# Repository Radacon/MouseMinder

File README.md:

# MouseMinder

MouseMinder is a small ATtiny10-based hardware project with a matching programming and test fixture. This repository combines the PCB design, fixture firmware, operator GUI, mechanical CAD exports, and simulation or validation data used to build and test the device.

## Repository Layout

- `codebase/`
  - Arduino Uno fixture firmware in `ardu_tiny_toaster.ino`
  - Base TPI programmer implementation in `tiny10_base_code.ino`
  - Operator desktop GUI in `gui.py`
  - Early or alternate device firmware work under `AtmelStudio/`
- `pcb_design/`
  - Main MouseMinder KiCad project files:
    - `MouseMinder.kicad_sch`
    - `MouseMinder.kicad_pcb`
    - `MouseMinder.kicad_pro`
  - Fixture or shield PCB design under `MouseMinder_Programmer_Shield/`
  - Archived KiCad backups under `MouseMinder-backups/`
  - Older release archives under `mouseminder_prev_versions/`
- `mechanical_design/`
  - Enclosure and trap body STEP exports under `trap_body/`
  - Accessory parts such as the battery isolator under `accessories/`
- `sim_and_test/`
  - Power profiling captures under `PowerProfilerData/`
  - Simulation exports under `Simulation/`

## Hardware Overview

The main board centers on an `ATtiny10-TS` and includes:

- A coin-cell battery holder
- A buzzer
- An LED indicator
- Two pushbuttons
- A discrete power or latching section around `Q1`

The repository also includes a separate programmer shield design and a fixture workflow for flashing and validating boards during bring-up or production.

## PCB Design Files

Primary electrical design assets live in `pcb_design/`:

- `MouseMinder.kicad_sch`
- `MouseMinder.kicad_pcb`
- `MouseMinder.kicad_pro`

Related hardware history is split out into:

- `pcb_design/MouseMinder_Programmer_Shield/` for the programming fixture PCB
- `pcb_design/MouseMinder-backups/` for KiCad backup archives
- `pcb_design/mouseminder_prev_versions/` for older packaged revisions

## Firmware And GUI

The programming and test fixture is built around an Arduino Uno and a Python desktop GUI.

Arduino-side files in `codebase/`:

- `ardu_tiny_toaster.ino`: fixture control firmware
- `tiny10_base_code.ino`: base TPI programming support for ATtiny4/5/9/10/20/40 devices

Desktop-side files in `codebase/`:

- `gui.py`: operator GUI for selecting firmware, discovering the fixture over serial, and running the programming loop
- `requirements.txt`: original behavior notes for the GUI and fixture

There is also an Atmel Studio project under `codebase/AtmelStudio/MouseMinder/` with a `main.c` firmware entry point and generated debug outputs.

## Fixture I/O Mapping

The current fixture firmware uses:

- `D10` -> `!RST`
- `D11/D12` -> `TPIDATA`
- `D13` -> `TPICLK`
- `A0` -> `BATT`
- `A1` -> `LATCHED`

The operator GUI is intended to:

- Auto-discover the Arduino fixture over available COM ports
- Show connection and pin-state information
- Let the operator select a `.hex` file
- Run the detect, program, verify, and test loop

## Mechanical Assets

Mechanical CAD exports are grouped under `mechanical_design/`:

- `trap_body/` contains enclosure and body STEP files, including lid and clip geometry
- `accessories/` contains supporting parts such as `Battery_Isolator_debossed.STEP`

## Simulation And Validation Data

Supporting measurement and simulation files live in `sim_and_test/`:

- `PowerProfilerData/` contains sleep-current or power measurement CSV files
- `Simulation/` contains scope and waveform export data from circuit simulation work

## Typical Workflow

1. Open the main hardware in `pcb_design/MouseMinder.kicad_sch` and `pcb_design/MouseMinder.kicad_pcb`.
2. Load the Arduino fixture firmware from `codebase/ardu_tiny_toaster.ino`.
3. Launch the operator GUI from `codebase/gui.py`.
4. Connect the programming fixture and target board.
5. Select a target `.hex` file and run the programming and test cycle.

## Running The GUI

Install the required Python package, then launch the GUI:

```powershell
pip install pyserial
python codebase\gui.py
```

The GUI depends on:

- `pyserial`
- Python standard library `tkinter`

## Fastest Entry Points

If you are picking up the project fresh, start with:

- `pcb_design/MouseMinder.kicad_sch`
- `pcb_design/MouseMinder.kicad_pcb`
- `codebase/ardu_tiny_toaster.ino`
- `codebase/gui.py`

## PMS150C Firmware Releases

Production PMS150C firmware is published only from tags named `firmware-vMAJOR.MINOR.PATCH` that point to a commit already on `main`. The tag-only GitHub Actions workflow builds `codebase/VSCODE_FreePDK` and publishes three immutable release assets:

- `slowclocksleep_PMS150C.bin`
- `slowclocksleep_PMS150C.bin.sha256`
- `mouseminder-firmware.json`

The manifest records the full commit, build toolchain, PMS150C memory contract, calibration target, asset size, and SHA-256. The production programmer must still require explicit WordPress administrator approval and verify the downloaded binary against the approved manifest before programming.

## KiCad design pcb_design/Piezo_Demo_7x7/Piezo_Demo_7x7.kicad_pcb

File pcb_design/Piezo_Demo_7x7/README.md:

# Piezo Demo 7x7

- KiCad 9 schematic and fully routed two-layer PCB.
- 224 mm x 224 mm board with a 7 x 7 grid of 32 mm cells.
- 43 buzzer footprints, two rows of seven MouseMinder SMD selector buttons, a vertical BNC input, and a reserved switching/MCU cell.
- Available EasyEDA 3D bodies are included and linked project-relatively.
- The BNC includes a simplified project-local preview body based on the TE product envelope.
- Front silkscreen: cell and MPN.
- Back silkscreen: MPN, LCSC number, live LCSC 1-piece/500-piece unit pricing, voltage, current, SPL, driver type, mount, and body size.

Five unavailable EasyEDA records use same-family fallback geometry. Verify every footprint against the purchased part's current datasheet before fabrication.

The schematic directly connects the BNC through one selected row switch and one selected column switch. Press one button from each bank to connect the corresponding buzzer. G2-G7 are unused.

ERC and PCB DRC both pass with zero violations and zero unconnected pads. JLCPCB-ready Gerbers are in `fabrication/Piezo_Demo_7x7_JLCPCB_Gerbers.zip`.

Regenerate with KiCad's bundled Python:

```powershell
python .\generate_bnc_model.py
& 'C:\Program Files\KiCad\9.0\bin\python.exe' .\generate_piezo_demo_board.py
python .\generate_piezo_demo_schematic.py
```

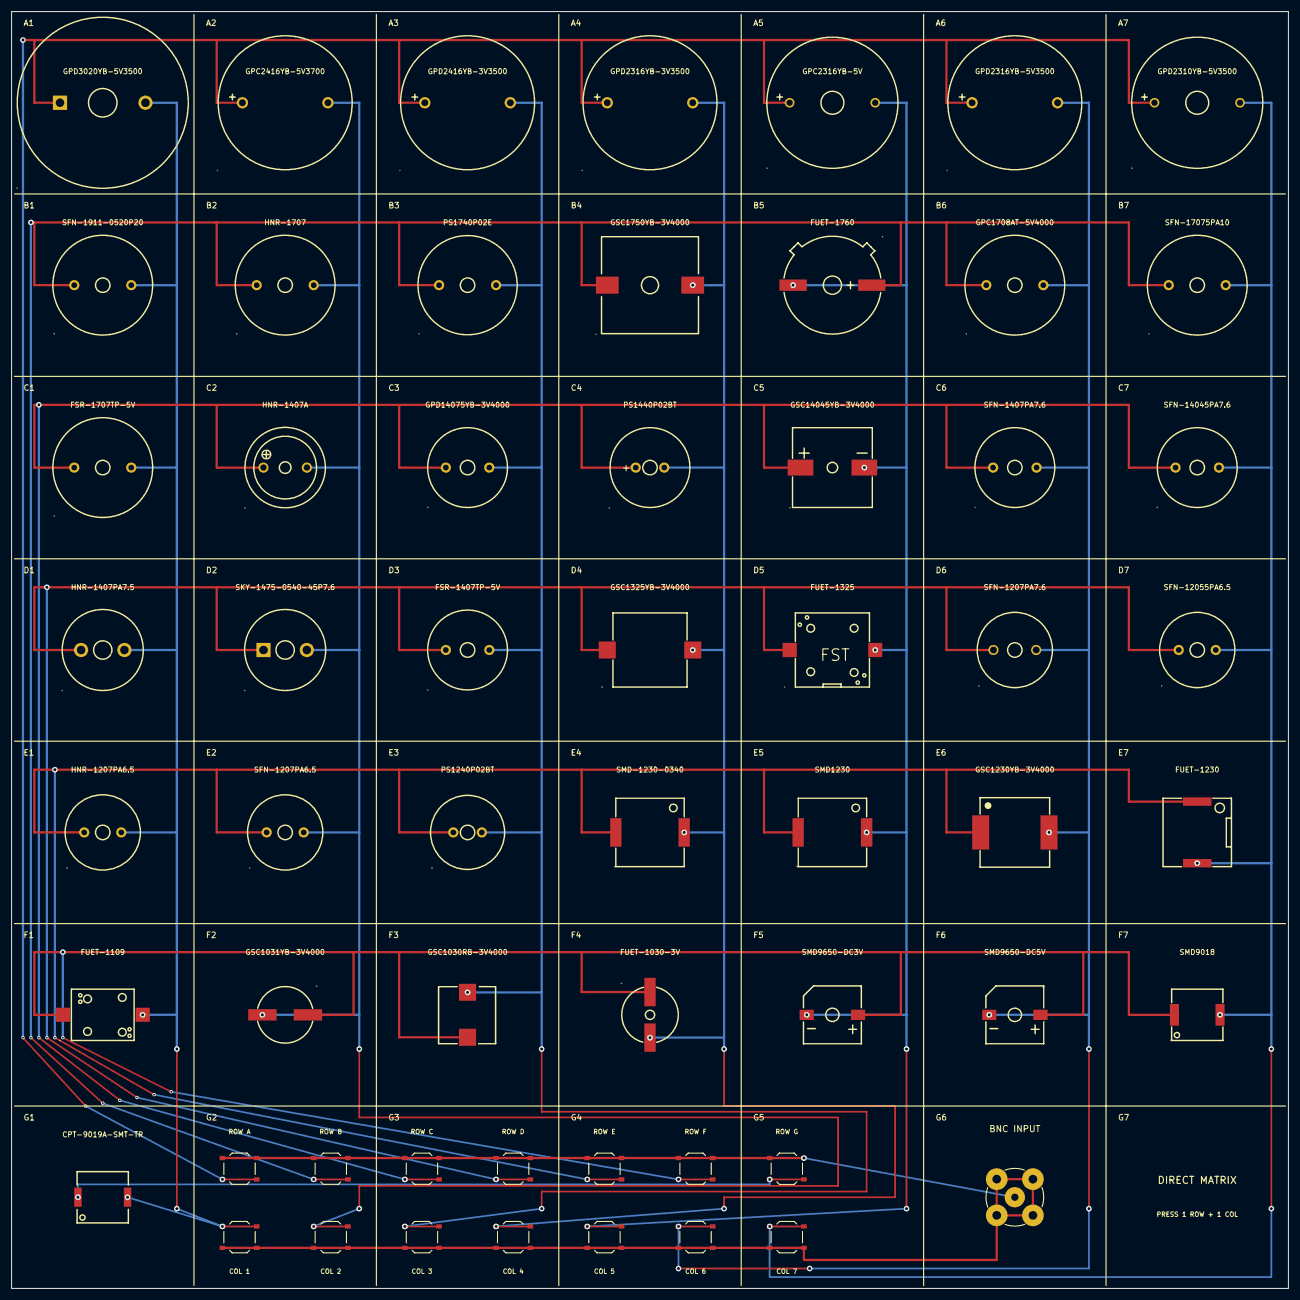
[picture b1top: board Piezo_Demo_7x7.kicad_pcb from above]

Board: 2 copper layers, 224.0 x 224.0 mm, 58 parts (0 on the bottom side), 16 nets.

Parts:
BZ1: GPD3020YB-5V3500; BUZ-TH_BD30.0-P15.00-D0.8
BZ2: GPC2416YB-5V3700; BUZ-TH_BD23.5-P15.00-D0.8-FD
BZ3: GPD2416YB-3V3500; BUZ-TH_BD23.5-P15.00-D0.8-FD
BZ4: GPD2316YB-3V3500; BUZ-TH_BD23.5-P15.00-D0.8-FD
BZ5: GPC2316YB-5V; BUZ-TH_BD23.0-P15.00-D0.8-FD
BZ6: GPD2316YB-5V3500; BUZ-TH_BD23.5-P15.00-D0.8-FD
BZ7: GPD2310YB-5V3500; BUZ-TH_BD23.0-P15.00-D0.8-FD
BZ8: SFN-1911-0520P20; BUZ-TH_BD17.0-P10.00-D0.9
BZ9: HNR-1707; BUZ-TH_BD17.0-P10.00-D0.9
BZ10: PS1740P02E; BUZ-TH_BD17.0-P10.00-D0.8
BZ11: GSC1750YB-3V4000; BUZ-SMD_L17.0-W17.0
BZ12: FUET-1760; BUZZ-SMD_FUET-1760
BZ13: GPC1708AT-5V4000; BUZ-TH_BD17.0-P10.00-D0.9
BZ14: SFN-17075PA10; BUZ-TH_BD17.0-P10.00-D0.9
BZ15: FSR-1707TP-5V; BUZ-TH_BD17.0-P10.00-D0.9
BZ16: HNR-1407A; BUZ-TH_BD14.1-P7.62-D1.0-FD
BZ17: GPD14075YB-3V4000; BUZ-TH_BD14.0-P7.60-D0.7-FD
BZ18: PS1440P02BT; BUZ-TH_BD14.0-P5.00-D0.7-FD
BZ19: GSC14045YB-3V4000; BUZ-SMD_L14.1-W14.1-LS14.9
BZ20: SFN-1407PA7.6; BUZ-TH_BD14.0-P7.60-D0.7
BZ21: SFN-14045PA7.6; BUZ-TH_BD14.0-P7.60-D0.7
BZ22: HNR-1407PA7.5; BUZ-TH_BD14.0-P7.60-D0.8-L
BZ23: SKY-1475-0540-45P7.6; BUZ-TH_BD14.0-P7.60-D1.0-L
BZ24: FSR-1407TP-5V; BUZ-TH_BD14.0-P7.60-D0.7
BZ25: GSC1325YB-3V4000; BUZ-SMD_L13.0-W13.0
BZ26: FUET-1325; BUZ-SMD_FST-1325
BZ27: SFN-1207PA7.6; BUZ-TH_BD12.6-P7.50-D0.9
BZ28: SFN-12055PA6.5; BUZ-TH_BD12.5-P6.50-D0.9
BZ29: HNR-1207PA6.5; BUZ-TH_BD12.5-P6.50-D0.9
BZ30: SFN-1207PA6.5; BUZ-TH_BD12.5-P6.50-D0.9
BZ31: PS1240P02BT; BUZ-TH_BD12.5-P5.00-D0.9
BZ32: SMD-1230-0340; BUZ-SMD_L12.0-W12.0
BZ33: SMD1230; BUZ-SMD_L12.0-W12.0
BZ34: GSC1230YB-3V4000; BUZ-SMD_L12.0-W12.0_CPT-12123-81-SMT-TR
BZ35: FUET-1230; BUZ-SMD_L12.0-W12.0_FUET-1230
BZ36: FUET-1109; BUZ-SMD_FST-1109
BZ37: GSC1031YB-3V4000; BUZ-SMD_BD10.0-P8.00-LS11.0
BZ38: GSC1030RB-3V4000; BUZ-SMD_L10.0-W10.0_GSC1030RB-3V4000
BZ39: FUET-1030-3V; BUZ-SMD_FUET-1030-XXV
BZ40: SMD9650-DC3V; BUZ-SMD_L9.6-W9.6-LS10.0-R
BZ41: SMD9650-DC5V; BUZ-SMD_L9.6-W9.6-LS10.0-R
BZ42: SMD9018; BUZ-SMD_L9.0-W9.0-P8.00-LS9.3
BZ43: CPT-9019A-SMT-TR; BUZ-SMD_L9.0-W9.0_CPT-9019A-SMT-TR
J1: 1-1478204-0; BNC_TEConnectivity_1478204_Vertical
SW1, SW2, SW3, SW4, SW5, SW6, SW7, SW8, SW9, SW10, SW11, SW12, SW13, SW14: LCK-TA022H18-2WL; SW_Push_1P1T_XKB_TS-1187A

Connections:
BNC_RETURN: J1.2, SW8.2, SW9.2, SW10.2, SW11.2, SW12.2, SW13.2, SW14.2
BNC_SIGNAL: J1.1, SW1.1, SW2.1, SW3.1, SW4.1, SW5.1, SW6.1, SW7.1
COL_1: BZ1.2, BZ8.2, BZ15.2, BZ22.2, BZ29.2, BZ36.2, BZ43.2, SW8.1
COL_2: BZ2.2, BZ9.2, BZ16.2, BZ23.2, BZ30.2, BZ37.2, SW9.1
COL_3: BZ3.2, BZ10.2, BZ17.2, BZ24.2, BZ31.2, BZ38.2, SW10.1
COL_4: BZ4.2, BZ11.2, BZ18.2, BZ25.2, BZ32.2, BZ39.2, SW11.1
COL_5: BZ5.2, BZ12.2, BZ19.2, BZ26.2, BZ33.2, BZ40.2, SW12.1
COL_6: BZ6.2, BZ13.2, BZ20.2, BZ27.2, BZ34.2, BZ41.2, SW13.1
COL_7: BZ7.2, BZ14.2, BZ21.2, BZ28.2, BZ35.2, BZ42.2, SW14.1
ROW_A: BZ1.1, BZ2.1, BZ3.1, BZ4.1, BZ5.1, BZ6.1, BZ7.1, SW1.2
ROW_B: BZ8.1, BZ9.1, BZ10.1, BZ11.1, BZ12.1, BZ13.1, BZ14.1, SW2.2
ROW_C: BZ15.1, BZ16.1, BZ17.1, BZ18.1, BZ19.1, BZ20.1, BZ21.1, SW3.2
ROW_D: BZ22.1, BZ23.1, BZ24.1, BZ25.1, BZ26.1, BZ27.1, BZ28.1, SW4.2
ROW_E: BZ29.1, BZ30.1, BZ31.1, BZ32.1, BZ33.1, BZ34.1, BZ35.1, SW5.2
ROW_F: BZ36.1, BZ37.1, BZ38.1, BZ39.1, BZ40.1, BZ41.1, BZ42.1, SW6.2
ROW_G: BZ43.1, SW7.2

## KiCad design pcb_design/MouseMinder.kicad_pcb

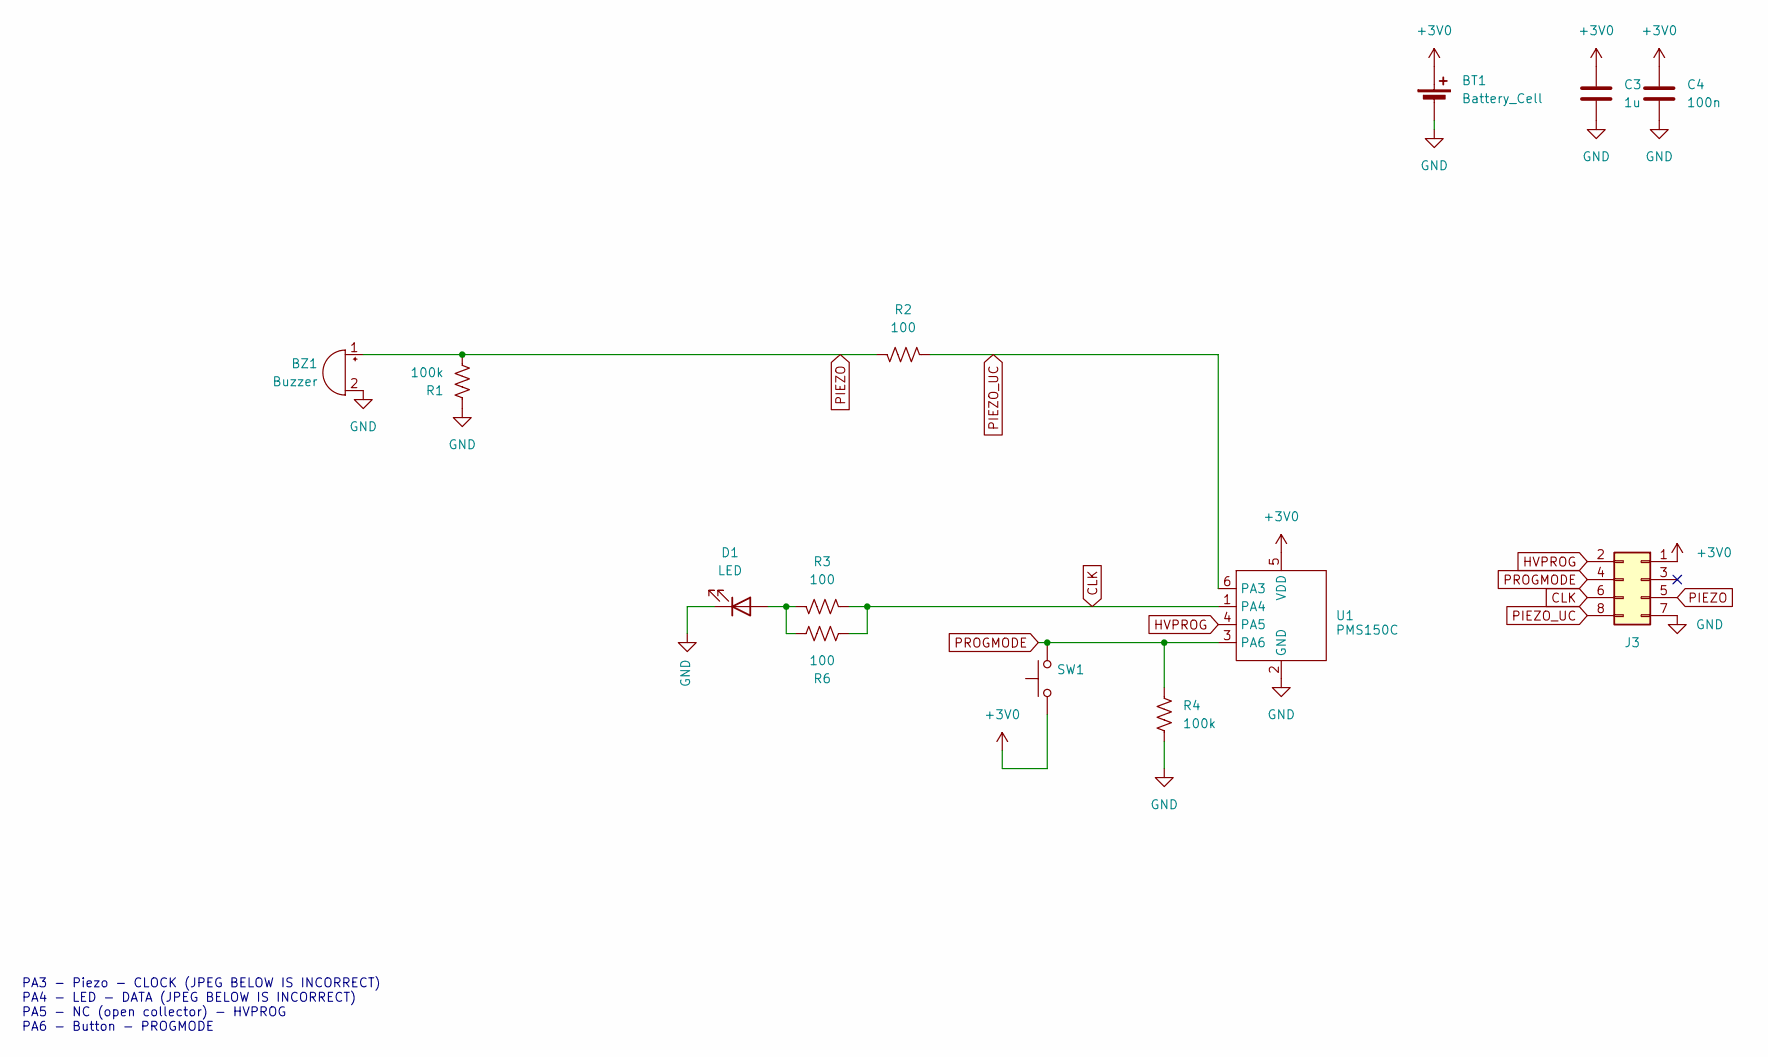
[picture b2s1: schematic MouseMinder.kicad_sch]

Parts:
BT1: Battery_Cell; MY-2032-08; MPN C964832; JLC_MPN C964832
BZ1: Buzzer; GSC1230YB-3V4000; MPN C255333; JLC_MPN C255333
C3: 1u; C_0603_1608Metric; MPN C1592; JLC_MPN C1592
C4: 100n; C_0603_1608Metric; MPN C2909627; JLC_MPN C2909627
D1: LED; XL-2810UYC; MPN C3646949; JLC_MPN C3646949
J3: Conn_02x04_Odd_Even; 2x8_POGO_CENTERING_HOLES
R1, R4: 100k; R_0603_1608Metric; MPN C25803; JLC_MPN C25803
R2, R3, R6: 100; R_0603_1608Metric; MPN C2785067; JLC_MPN C2785067
SW1: LCK-TA022H18-2WL; SW_Push_1P1T_XKB_TS-1187A; MPN C51978285; JLC_MPN C51978285
U1: PMS150C; SOT-23-6; MPN C168658; JLC_MPN C168658

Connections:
+3V0: BT1.1 (+), C3.1, C4.1, J3.1, SW1.1, U1.5 (VDD)
CLK: J3.6, R3.1, R6.1, U1.1 (PA4)
GND: BT1.2 (-), BZ1.2 (-), C3.2, C4.2, D1.1 (K), J3.7, R1.1, R4.2, U1.2 (GND)
HVPROG: J3.2, U1.4 (PA5)
unnamed: D1.2 (A), R3.2, R6.2
PIEZO: BZ1.1 (+), J3.5, R1.2, R2.2
PIEZO_UC: J3.8, R2.1, U1.6 (PA3)
PROGMODE: J3.4, R4.1, SW1.2, U1.3 (PA6)

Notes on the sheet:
PA3 - Piezo - CLOCK (JPEG BELOW IS INCORRECT) PA4 - LED - DATA (JPEG BELOW IS INCORRECT) PA5 - NC (open collector) - HVPROG PA6 - Button - PROGMODE

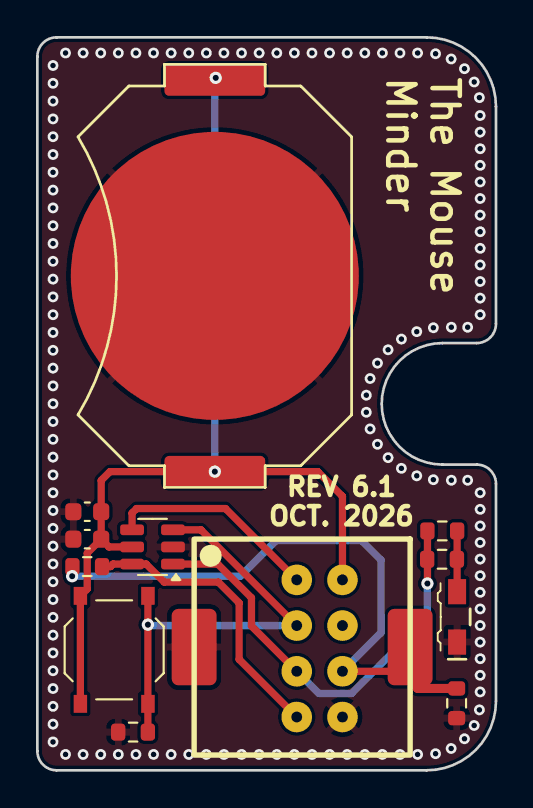
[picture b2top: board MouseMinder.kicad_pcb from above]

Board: 2 copper layers, 25.5 x 40.7 mm, 13 parts (1 on the bottom side), 8 nets.

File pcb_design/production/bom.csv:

Designator,Footprint,Quantity,Value,LCSC Part #
BT1,MY-2032-08,1,Battery_Cell,C964831 
BZ1,GSC1230YB-3V4000,1,Buzzer,C255333
C3,0603,1,1u,C1592
C4,0603,1,100n,C14663
D1,XL-2810UYC,1,LED,C3646949
"R1, R4",0603,2,100k,C25803
"R2, R3, R6",0603,3,100,C22775
SW1,SW_Push_1P1T_XKB_TS-1187A,1,LCK-TA022H18-2WL,C51978285
U1,SOT-23-6,1,PMS150C,C168658

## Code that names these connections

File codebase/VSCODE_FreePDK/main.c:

/*
  MouseMinder low-power alarm

  PMS150C-U06

  PA6: sleep/wake pushbutton, externally pulled low, switch to VDD
  PA4: LED, active high
  PA3: piezo input while quiet; Timer2 tone output while sounding
*/

#include <stdint.h>
#include "sdcc_intellisense.h"
#include <pdk/device.h>

#include "auto_sysclock.h"
#include "startup.h"
#include "delay.h"
#include "chirp_pattern.h"

#if CHIRP_MASTER_CLOCK_HZ != F_CPU
#error "chirp_pattern.h clock does not match the firmware F_CPU"
#endif

#if CHIRP_TIMER_DIVIDER != 1
#error "The firmware chirp player currently requires timer divider 1"
#endif

/*------------------------------------------------------------------
  User tuning
 ------------------------------------------------------------------*/

#define LED_PULSE_MS               10u
#define EVENT_SLEEP_MS           1000u
#define LED_FLASHES_PER_CHIRP       5u

/*------------------------------------------------------------------
  Pins
 ------------------------------------------------------------------*/

#define PIEZO_BIT                   3u
#define LED_BIT                     4u
#define BUTTON_BIT                  6u

#define PIEZO_MASK          (1u << PIEZO_BIT)
#define LED_MASK            (1u << LED_BIT)
#define BUTTON_MASK         (1u << BUTTON_BIT)

#define turnLedOn()         (PA |= LED_MASK)
#define turnLedOff()        (PA &= (uint8_t)~LED_MASK)
#define buttonIsPressed()   ((PA & BUTTON_MASK) != 0)

/*------------------------------------------------------------------
  Timer16 timed STOPEXE sleep
 ------------------------------------------------------------------*/

/*
 * Timer16 uses undivided ILRC and wakes on the rising edge of bit 15.
 * Each preload stays below 0x8000, making that rising edge the next bit-15
 * transition.  Longer delays are split into 500 ms sleeps below.
 */
#define TIMER16_SLEEP_CONFIG \
    (T16M_CLK_ILRC | T16M_CLK_DIV1 | T16M_INTSRC_15BIT)

#if (F_CPU % 1000u) != 0
#error "Timer16 millisecond sleeps require F_CPU divisible by 1000"
#endif

#define ILRC_TICKS_PER_MS (F_CPU / 1000u)

#if ILRC_TICKS_PER_MS != 52u
#error "Update millisecondsToTicks for the configured F_CPU"
#endif

static uint16_t timer16Load;

static void piezoInput(void)
{
    TM2C = TM2C_CLK_DISABLE;
    INTRQ &= (uint8_t)~INTRQ_TM2;
    PA &= (uint8_t)~PIEZO_MASK;
    PAC &= (uint8_t)~PIEZO_MASK;
}

static uint8_t activeLedPulseDelay(void)
{
    PADIER = BUTTON_MASK;

    /*
     * This helper is used only with compile-time constants.  Staying awake
     * here matches the ATtiny's _delay_ms() cadence and avoids PMS150C
     * STOPEXE wake-up latency on short delays.
     */
    _delay_ms(LED_PULSE_MS);

    return buttonIsPressed();
}

static uint8_t sleepTicks(uint16_t ticks, uint8_t piezoWake)
{
    uint8_t buttonPressed;

    T16M = (uint8_t)TIMER16_SLEEP_CONFIG;
    timer16Load = (uint16_t)(32768u - ticks);
    __asm
        stt16 _timer16Load
    __endasm;
    INTEGS &= (uint8_t)~INTEGS_T16_FALLING;
    INTRQ &= (uint8_t)~INTRQ_T16;

    /*
     * PA6 always wakes active waits.  PA3 also wakes quiet waits, but is
     * excluded while Timer2 is driving the tone.
     */
    PADIER = (uint8_t)(BUTTON_MASK |
                      (piezoWake ? PIEZO_MASK : (uint8_t)0u));

    __asm
        stopexe
    __endasm;

    /* Read PA6 before disabling its digital input buffer. */
    buttonPressed = buttonIsPressed();
    PADIER = 0;
    INTRQ &= (uint8_t)~INTRQ_T16;

    return buttonPressed;
}

static uint8_t sleepMilliseconds(uint16_t milliseconds, uint8_t piezoWake)
{
    uint16_t ticks;

    while (milliseconds > 500u)
    {
        if (sleepTicks((uint16_t)(F_CPU / 2u), piezoWake))
            return 1;

        milliseconds -= 500u;
    }

    if (!milliseconds)
        return 0;

    /* 52 ticks/ms = 32 + 16 + 4; avoid SDCC's multiply helper. */
    ticks = (uint16_t)((milliseconds << 5) +
                       (milliseconds << 4) +
                       (milliseconds << 2));

    return sleepTicks(ticks, piezoWake);
}

/*------------------------------------------------------------------
  Piezo tone
 ------------------------------------------------------------------*/

static void startTone(uint8_t timerDivisor)
{
    /* Keep the PA6 button readable; PA3 is driven by Timer2. */
    PADIER = BUTTON_MASK;
    PAC |= PIEZO_MASK;
    TM2CT = 0;
    TM2B = (uint8_t)(timerDivisor - 1u);
    TM2S = TM2S_PRESCALE_NONE | TM2S_SCALE_NONE;
    TM2C = TM2C_CLK_ILRC | TM2C_MODE_PERIOD | TM2C_OUT_PA3;
}

static uint8_t startupChirps(void)
{
    uint16_t offset = 0;
    uint8_t step = CHIRP_STEP_COUNT;

    while (step--)
    {
        uint8_t timerDivisor = chirpPattern[offset];
        uint16_t duration = (uint16_t)chirpPattern[offset + 1u] |
                            ((uint16_t)chirpPattern[offset + 2u] << 8);
        offset += CHIRP_STEP_BYTES;

        if (timerDivisor)
            startTone(timerDivisor);
        else
            piezoInput();

        PADIER = BUTTON_MASK;
        while (duration--)
        {
            _delay_ms(1);
            if (buttonIsPressed())
            {
                piezoInput();
                return 1;
            }
        }
    }

    piezoInput();
    return 0;
}

/*------------------------------------------------------------------
  Deep sleep
 ------------------------------------------------------------------*/

static void waitForButtonRelease(void)
{
    PADIER = BUTTON_MASK;

    while (buttonIsPressed())
    {
        T16M = T16M_CLK_DISABLE;

        __asm
            stopexe
        __endasm;
    }

    PADIER = 0;
}

static void deepSleep(void)
{
    uint8_t buttonPressed;

    turnLedOff();
    piezoInput();
    T16M = T16M_CLK_DISABLE;

    /*
     * PMS150C GPIO sleep wake detects a pin transition rather than a
     * selectable edge.  With PA6 externally pulled low, software accepts
     * the high level as the wake-button press.
     */
    PADIER = BUTTON_MASK | PIEZO_MASK;

    __asm
        stopsys
    __endasm;

    /* Determine whether PA6 or the PA3 piezo caused the wake. */
    buttonPressed = buttonIsPressed();
    PADIER = 0;

    /* Do not interpret the same held button press as an immediate off. */
    if (buttonPressed)
        waitForButtonRelease();
}

/*------------------------------------------------------------------
  Setup and active pattern
 ------------------------------------------------------------------*/

static void setup(void)
{
    /* LED off; button and piezo initially inputs. */
    PA = 0;
    PAC = LED_MASK;
    PAPH = 0;
    PADIER = 0;

    GPCC = 0;
    GPCS = 0;
    TM2C = 0;
    T16M = 0;

    MISC |= MISC_LVR_DISABLE;

    /*
     * PA5 reset, watchdog and IHRC are disabled.  ILRC remains the system
     * clock and is automatically stopped by STOPSYS.
     */
    CLKMD &= (uint8_t)~(CLKMD_ENABLE_PRSTB |
                        CLKMD_ENABLE_WATCHDOG |
                        CLKMD_ENABLE_IHRC);

    INTEN = 0;
    INTRQ = 0;
}

static uint8_t activeAlert(void)
{
    uint8_t flashCount = 0;

    while (1)
    {
        turnLedOn();

        if (activeLedPulseDelay())
        {
            turnLedOff();
            return 1;
        }

        turnLedOff();

        if (++flashCount >= LED_FLASHES_PER_CHIRP)
        {
            flashCount = 0;

            if (startupChirps())
                return 1;
        }

        /*
         * Match the ATtiny cadence: the approximately one-second sleep
         * begins after the LED pulse and any scheduled chirp.
         */
        if (sleepMilliseconds(EVENT_SLEEP_MS, 0))
            return 1;
    }
}

void main(void)
{
    setup();

    while (1)
    {
        /* Power-up and every wake begin with the introductory beep pattern. */
        if (startupChirps())
        {
            waitForButtonRelease();
            deepSleep();
            continue;
        }

        activeAlert();
        waitForButtonRelease();
        deepSleep();
    }
}

/*------------------------------------------------------------------
  Startup
 ------------------------------------------------------------------*/

unsigned char STARTUP_FUNCTION(void)
{
    AUTO_INIT_SYSCLOCK();
    AUTO_CALIBRATE_SYSCLOCK(TARGET_VDD_MV);

    return 0;
}

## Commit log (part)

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2026-04-10 added gitignore
2026-04-10 First Commit!
2026-04-10 cleaning
2026-04-10 had ai refactor the readme
2026-04-12 First commit baby!
2026-04-12 nuked my old repo. inadvertantely removed all old files. Made a backup, restoring backup
2026-04-12 now we can pull the hex from github. Will use this for embedding the hash into the firmware for hardware tracking
2026-04-12 Gui tweaks. Added in some pass-fail logic and am still working on the clear memory command and read metadata command
2026-04-12 debugging on if I can actually re-program these guys...
2026-04-12 Now have git hash writing working as well as chip erasure as well as reading metadata from flash!
